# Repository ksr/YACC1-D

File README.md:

# YACC1-D — the definitive YACC1 tree

**Status (2026-09-28):** the single source of truth for YACC1, on GitHub at `github.com/ksr/YACC1-D`, migrated from
the old `YACCS/` folders on 2026-09-19/20. What is in the machine today: `docs/system/MACHINE.md`; which board
revisions exist and were made: `hardware/FABRICATED.md`; what is open: `BACKLOG.md`.

**Who made it:** YACC1 is my project: I designed and built the hardware and wrote the original microcode, monitor,
Tiny BASIC and emulator. Claude, Anthropic's AI, has been directly involved in the design, coding and documentation
since 2026; the header at the top of every source file says who wrote it. — Ken Rother

**Working on it:** `CLAUDE.md` (the working notes for Claude sessions) has the standing rules, the machine facts that
bite, where things are and how to build and test. On a new Mac: clone, `python3 tools/setup_check.py` (which tools are
missing, and the command for each), `make` (the C tools), then `make check`.

## What YACC1 is

YACC1 ("Yet Another Custom CPU") is a hand-built 8-bit TTL computer: an 8-bit accumulator and TMP register, eight
16-bit registers R0-R7, microcoded, on a 96-pin bus. The cards: backplane, a two-board sequencer (logic + microcode
memory), ALU, two index-register cards, memory (RAM, the 8K ROM, TMP registers), I/O (16550 UART console, switches,
LEDs, TIL311s), a 6845 video card (working since 2026-10-21; its VGA successor, V4, designed and not ordered), and
a bus tester for driving the bus by hand.

Around the hardware, all in this tree:

- **Firmware in the machine:** the microcode (a C generator that writes the sequencer's EEPROM image), the monitor
  ROM with its Intel-hex loader, BIOS vectors and video driver, and a Tiny BASIC.
- **Y1/OS:** a disk operating system on CompactFlash (P8XFS), with a shell, redirection and pipes, and some thirty-five
  `/bin` commands, most ported from P8X, among them `vi`, `sed`, `awk`, `pack` and `kermit`. It exists twice and is kept
  in step: `os/y1os.asm` (the real one) and `os/y1os.c` (its specification).
- **y1cc**, a C compiler for YACC1: a Python reference, a C twin, and nine passes that run under Y1/OS. Together with
  the on-target assembler `/bin/asm` they rebuild themselves byte for byte on the emulator (the self-host).
- **Host tools:** the RC/asm assembler, an instruction-level emulator, a microcode-level emulator that steps the real
  EEPROM image through models of the cards, loaders for the ROM monitor and the sequencer card, Kermit, the CF-card
  writer, and the KiCad board tooling.

Before this tree the work was spread over nine overlapping copies under `YACCS/` (Eagle variants, four git clones with
different histories, backups). YACC1-D keeps the *current* version of every board, program, tool, test and document in
one place, with everything superseded kept but frozen. `MIGRATION.md` and `migration/` record where every file came
from.

## The tree

```
YACC1-D/
├── README.md  CLAUDE.md  BACKLOG.md  MIGRATION.md
├── Makefile                  make (the C tools), make check (everything, ~11 min), os-test, cc-test, native-test, ...
├── docs/
│   ├── system/               MACHINE.md (what is built), architecture, memory map, microcode, OS plan
│   ├── isa/                  a timing diagram per instruction, the microcode review
│   ├── cards/                theory of operation, one per card
│   ├── programming/          assembler, monitor, OS, C compiler, emulators, memory map, I/O ports
│   ├── procedures/           bring-up, CF card, testing, Kermit
│   ├── bom/                  bills of material, one per card
│   ├── history/              dated design notes kept verbatim (2016-2021), presentations
│   ├── datasheets/           the list of third-party datasheets (the PDFs: ../private-resources/YACC1-D/)
│   └── references/           external papers and books
├── hardware/
│   ├── bus/                  backplane, bus template, bus jumpers, blank card
│   ├── cards/<card>/         one folder per card (below)
│   ├── libraries/            eagle/: the Eagle .lbr/.dru files the designs use
│   ├── mechanical/           card divider clips, switch template, spacers
│   ├── FABRICATED.md         every revision of every board: built, in the machine, or design only
│   ├── SCHEMATICS.md BOARDS.md   generated indexes of the schematic and board PDFs
│   ├── KICAD.md              the Eagle -> KiCad conversion and its netlist proof
│   └── reviews/              the indexes of the multi-card design reviews (2026-09-21: mechanical, datapath,
│                             control and I/O); the reviews themselves are in each board's own reviews/
├── firmware/                 code that runs INSIDE the machine
│   ├── microcode/            ucode-generator2 (C) -> test.hex, the sequencer EEPROM image
│   ├── monitor/  basic/      monitor.asm, basic.asm (+ candidates never burned)
│   ├── rom/                  shipped/ (the image to burn and what is burned), builds/, captured chips
│   └── abi/                  BIOS vectors, variable and port map (still to be written)
├── os/                       Y1/OS: y1os.asm + y1os.c, commands/ (C), commands-asm/ (asm.asm, basic.asm), lib_*.c,
│                             man/, docs/, Makefile -> os/disk.img
├── software/                 host-side toolchain (runs on the Mac)
│   ├── assembler/            RC/asm + yacc1.def
│   ├── emulator/             instruction-level emulator (the ISA reference)
│   ├── ucemu/                microcode-level emulator (test.hex through models of the cards, CF, video)
│   ├── y1dbg/                the debugger for ucemu (y1ucemu -D + a curses UI with the live video screen)
│   ├── gatemodel/            cards at gate level from their netlists (the video card for y1ucemu -G)
│   ├── compiler/             y1cc.py, c/ (y1cc.c and the passes cc1..cc9), lib/
│   ├── disassembler/         disasm2
│   └── ubasic-c/             the C uBASIC the assembly BASIC was ported from
├── embedded/                 Arduino sketches for the support cards, built against libraries/ only
│   ├── sequencer-card/       sequencer4 (the microcode loader in the machine), dumpram, deprecated/
│   ├── bus-tester/           bus-driver, bus-monitor, bus-test, led-switch-test
│   ├── clocker/              external single-step clock
│   ├── command-sender/       Processing host for bus-tester scripts (to be replaced by Python)
│   └── libraries/            vendored: YACC_Common_header.h (bus table), Adafruit_MCP23017 1.1.0
├── tools/                    host scripts: setup_check, verify_firmware/embedded, ucode_send, monload, cfcard,
│                             y1kermit, p8xfs, the KiCad/Eagle tooling, the tree audit
├── tests/                    os, compiler, native (self-host), asm, disasm, bench (the machine), monload, kermit,
│                             cfcard, video, sequencer, ucemu, y1dbg, memory, assembler, bus-tester-scripts
├── mk/                       shared make fragments
├── migration/                the 2026-09-19/20 migration's inventory, plan and logs
├── vm/                       manifests of VMs and legacy installers (the images live outside git)
├── media/                    photos of the boards
├── website/                  the project website: MkDocs over these docs (website/README.md), live at yacc1.cottageworker.com
└── archive/                  frozen, never edited: gen1-2015-2018 (the first YACC1), superseded-revisions,
                              eagle-projects, third-party, conflict-losers (older duplicates from the migration)
```

## Card folder layout (`hardware/cards/<card>/`)

```
<card>/
├── README.md        what the card is, current revision, what is built, open issues
├── kicad/<rev>/     KiCad 10 projects, GENERATED from the Eagle files by tools/eagle_to_kicad_all.py with a
│                    schematic-vs-board netlist proof (hardware/KICAD.md) - except where a MASTER marker says the
│                    KiCad project is hand-maintained and IS the design (memory v2.0, CF v1.0, video v1.1);
│                    those have a build.sh (route with Freerouting, DRC, gerbers, renders, BOM)
├── eagle/<rev>/     the Eagle originals, frozen; the active revision at the top, fab/ (what was sent to the board
│                    house), pdf/ (generated), bom/
│   └── deprecated/  every older revision, same shape
├── reviews/         the card's design reviews, one file per review (<rev>-<review>-<date>.md, or <rev>.md)
└── docs/            card-specific notes
```

| Card | In the machine | Designed, not built |
|---|---|---|
| backplane | V2.0 (8 slots) | |
| sequencer-logic | v2.1 | v2.2 "CPU off" switch (idea, BACKLOG) |
| sequencer-memory | V2.1 + EEPROM adaptor | |
| alu | V3.2 | |
| register (index registers) | 1.1, two cards (R0-R3, R4-R7) | |
| io | V1.1 | |
| memory | v1.3 | **v2.0**: v1.3 + the CompactFlash interface on P8/P9, finished for fabrication |
| video | V1.0, no 6845 fitted yet | **v1.1** (KiCad master), changes still to make before ordering |
| cf | | v1.0, a separate CF card, superseded by memory v2.0 |
| bus-tester | V1.1 (2016; a bench tool) | V3.1 (2020, never ordered) |
| mem-switch, mem-register | bring-up cards (switch ROM at $0000, 16-byte RAM at $0010), fitted when needed | |
| protocard, address-tmp | built (address-tmp retired) | |

Bus items live under `hardware/bus/`: backplane, bus-template V3.2, bus jumpers (built, obsolete, not fitted), blank
card V3.1 (built) and V3.2 (the template for new cards).

## Conventions

- One authoritative copy of anything. Duplicates were the whole problem.
- Lower-case, hyphenated directory names; no spaces (the Eagle tree's spaces broke scripts repeatedly).
- Binary images (ROM, microcode hex) are committed **with** their source and a script that rebuilds them and
  diffs against the committed file; `make check` does it for all of them.
- Every file is explained: `tools/audit_tree.py` must report 0 unexplained after every commit.
- Files that came from YACCS are edited only with a dated entry in `tools/patched_files.txt`.
- Third-party code and libraries are vendored under a folder that says so, with their licence.
- Anything under `archive/` or `deprecated/` is never edited.
- Every `.rtf` note has a generated Markdown twin beside it (`tools/rtf_to_md.py`).
- No git LFS. Very large binaries (the 142 MB presentation, installers, VM images) live outside git, listed in `vm/`.

## How the migration was settled

- Repo: `~/Developer/YACC1-D` on both Macs (out of iCloud Drive, which corrupts `.git`), on GitHub, no LFS.
- History: started fresh (the first commit is the migration); the old `ksr/YACC1-2020` repo is not grafted in.
- `archive/` is committed (about 186 MB), and so are the datasheets.
- Older board revisions that were built stay with their card under `eagle/deprecated/`;
  `archive/superseded-revisions/` holds designs never built and the old tree's snapshots.
- Monitor and BASIC: the 2026 builds in `firmware/rom/shipped` are current; the 2021 `8afde21` build (ON/OFF, break-in)
  is kept as a candidate, never burned.
- Build environment: every C tool has a plain Makefile (2026-09-20); the NetBeans `nbproject/` folders are kept but
  no longer needed.

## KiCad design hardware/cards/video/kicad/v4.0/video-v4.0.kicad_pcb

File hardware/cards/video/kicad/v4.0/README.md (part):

# Video card V4.0 (6845, VGA, 16 dots a count) - the circuit, the schematic, the routed board

The circuit as data, checked and simulated; its schematic; and the board, 250 mm long, every part placed and
**every connection routed** (2026-11-12; reviewed, changed and routed again 2026-11-13; routed once more
2026-11-14, its four clocks laid first). Not ordered, not built. The pre-order check (`pcb-check`, 2026-11-14)
finds no failure and leaves one warning: "The pre-order check", below. Changed on the routed board since, no track
moved: the oscillator's pin 1 tied to +5 V (2026-11-18); a place that takes the oscillator in a can of either
size, and the labels by the power LED set apart (2026-11-20). `v40_netlist.py` is the card's circuit (parts, nets, the pins left open), written from the design note
`docs/cards/video-v4.md` (section 5 the clock and the stage, 6 the text, 7 the graphics RAM's two modes, 8 the dot
path, 9 the ports).

`python3 v40_netlist.py` checks the wiring (in `make check`): every pin of every part on a net or listed as open, no
net with a single pin, no two outputs on one net, an output on every net of ICs, a capacitor for every IC, and the
text-only build.

`tests/video/v40_netsim.py` (in `make check`, about two minutes) runs the netlist as a circuit, gate for gate, with every
part's delays from its data sheet at both ends of their ranges: the proof that the wiring does what the note says,
and the timing check. The parts in the netlist are the ones it was run with: a 74HCT or 74LS part in place of a 74F
or 74ACT one is another circuit.

**134 parts, 46 ICs** (V2.0 has 40, the V3 design 47).

| Block | ICs | |
|---|---|---|
| Bus, ports, registers | IC1-IC9 | block select (74S85), port decode (74LS138), the strobes (2 x 74LS32), control 1 and control 2 (2 x 74HCT273), the status (74LS244), inverters and ANDs (74HCT04, 74HCT08) |
| The 6845 and the clock | IC10-IC13, OSC1, R20-R23 | the 6845, the 25.175 MHz oscillator, the dot counter (74F163A), the 6845's clock and DE's delay (74F74), inverters (74ACT04); 33 ohm in series with the dot clock (R20), D2 (R21), D3 (R22) and the stage's clock (R23) |
| Text | IC14-IC23 | the text RAM (IDT7134), the stage (2 x 74ACT574), the code register (74ACT574), the character generator (AT28C64B-15), the shifter (74F299), the cursor flag and the retimed dot (74F74), the load (74F21), 74ACT86, 74ACT08 |
| Graphics, left off in the text-only build | IC24-IC34, RN2 | the address multiplexers (4 x 74ACT157), the RAM (AS6C1008-55), the write buffer (74ACT244), the read latch (74ACT574), direct mode's read buffer (74HCT244), the byte latch (74ACT574), the shifter (74F299), WRQ and TXTONLY (74F74) |
| Slot logic, dots, syncs | IC35-IC40 | P56 and the read latch's clock (74F74), 74ACT32, 74ACT00, 74ACT11, the guns (74ACT02), the vertical sync's length (74HCT74) |
| PS/2 | IC41-IC46 | V2.0's section: ATmega328P, two latches, the status, the flags, the 7416 |

The references are new (this card keeps none of V1.3's or V2.0's numbers); the PS/2 section's nets are V2.0's.

## The simulation (2026-11-12; the hold margins and the counted addresses 2026-11-13)

The simulator and the models of the 74F and 74ACT parts and of the 128K RAM are `tests/video/netsim.py` (first
written for the V3 design's check); added are the 74ACT157, the 74ACT244 with its enable times, the text RAM's display
port, the character generator, a 6845 that steps a script of counts and checks the clock it is given, and the bus
as the microcode drives it, started at every phase of the dot counter. Eight corners: the 6845 slow or fast, the
parts all slow or all fast, and the two mixed corners that set rising outputs against falling ones. A clock's
series resistor (R20-R23) is a part with a delay of 0.3 to 2 ns: the resistor, its net's load and the wire, as one.

51 runs, none failing: the picture (every count's two characters and two bytes, the cursor's half, blanking, OR and
XOR, the pages, the colour bits), the window in slot mode at 3.5 MHz and in direct mode at 6 MHz (a write and two
reads at each of 32 phases of the count, the picture going on undisturbed; once more at 160 phases, 4 ns apart),
a read whose address was counted in the step before (a stack or a BRVR vector table in the window) at 2.8 MHz,
switching the mode at every phase with nothing written, the text-only build, the ports and the status, the syncs.

| Closest margins, all runs | To spare |
|---|---|
| Hold: the 6845's clock flip-flop takes the counter's D3 (IC12 pin 2) | 2.0 ns |
| Hold: the vertical sync's second flip-flop takes the first's output (IC40 pin 12) | 2.0 ns |
| Hold: the shifters' data, as the code register and the byte latch take the next byte | 2.5 ns |
| Hold: the shifters' load, as it ends | 3.7 ns |
| The retimed dot: a shifter's output through two gates to the flip-flop (set-up) | 5.6 ns |
| Hold: the 74ACT574s (the byte latch the closest) | 9.6 ns |
| Hold: the read latch | 10.7 ns |
| The shifters' load (the mode input's set-up) | 14.7 ns |
| The RAM's write pulse, 69.6 ns at its shortest | 24.6 ns over the 45 wanted |
| The RAM's data before the pulse ends | 34.6 ns |
| A byte read in slot mode at 3.5 MHz, on the bus before it is taken (160 phases) | 40 ns |
| The RAM to the read latch (set-up) | 52.1 ns |
| The text RAM (as the 70 ns grade) to the code register | 61.9 ns |
| A byte read in direct mode at 6 MHz, on the bus before it is taken | 88 ns |

The holds of 2 to 4 ns are all of one kind: a flip-flop takes what another, on the same clock edge, is changing.
They rest on the senders' least delays (2.7 ns for the 74F163A, 1.5 ns for a 74ACT574) and do not shrink with the
frequency; what they need is a clock that reaches the taker no later than the sender. The simulation prints the
least hold of each kind since the design review (its V4-5), which found that the first table here left them out.

`--limits`: the window works down to a microcode step of 531 ns in slot mode (a CPU clock of 3.76 MHz) and 248 ns in
direct mode (8.07 MHz), the parts slow, for an address that a register selected in the step puts on the bus. For an
address counted in the step before - a stack or a BRVR vector table in the window - slot mode works to 3.15 MHz
(the count within the window) and 2.97 MHz (into it), direct mode to 5.69 and 5.15 MHz: the note's rule 2.
`--faults`: 23 wiring faults put into the netlist in memory, one at a time (crossed bits, a missing gate input, the
wrong polarity): every one is reported by a run.

Not in it: the 6845's own minimum delays (its sheet gives none; 20 ns assumed, and the stage has 19 ns of hold from
a 6845 that answers in no time), Hitachi's 6845 (the figures are Motorola's sheet), a delay for each wire (the four
clock nets have one each, with their resistors; the others none), signal quality on the bus, and a bench.

## What the simulation changed in the netlist

- **A write pulse is always whole.** As first written, -WE in slot mode contained the CPU's strobe (V2.0's way), so
  a strobe that ended inside a pulse cut it short: a -WE of any width down to nothing, at a moment when the RAM's
  data lines still hold the display's byte. Now WRQ alone opens the pulse (WEP# = NAND(WRQ, P56)) and direct mode has
  a gate of its own (WED#); the microcode's step of hold after the strobe covers the rest of the slot. WRQ is held
  clear in direct mode (it was preset), so no pulse can come as slot mode begins.
- **The -WE pulse's flip-flop** has its D from the 74F21 and the read latch's clock flip-flop from the 74ACT11
  (they were the other way round): the first had 6 ns of set-up to spare behind the inverter, and has 11 now.

## What the netlist settles that the note left open

- **The read latch's clock** is a flip-flop's pulse in dots 8 and 0 (RDCK, IC35/B), so the latch takes the RAM's byte
  as a CPU slot ends with the whole slot for the access. The latch is a 74ACT574 for its 1 ns hold time.
- **The cursor flag** is taken with each code (IC20/A); only DE is delayed (SDE2, as dot 8 begins).
- **The status's VSYNC and DE** (IN PC bits 1 and 2) are the stage's, a count behind the 6845's pins.
- **The vertical sync** at the connector lasts from the staged VSYNC's rise to the second HSYNC after it: about 1.8
  lines, with either maker's 6845.
- **The text-only build** needs no resistor of its own: R8, R9 and R10 are fitted in both builds.
- **46 ICs**, where the note's estimate was 42 or 43: four 74F74 where it counted two, and an inverter and an AND
  package more.

## What the design review changed (2026-11-13)

`../../reviews/v4.0.md`: HIGH 0, MED 4, LOW 12, INFO 7. Nothing found says the card will not work; its status table
has what was done with each finding. In the circuit and on the board:

- **A 33 ohm resistor in series with each of the four clocks that cross the board**: R20 at the oscillator (the dot
  clock, seven 74F clock inputs), R21 and R22 at the counter's outputs (D2, D3), R23 at the inverter that makes the
  stage's clock. The nets between a source and its resistor are OSCO, QC, QD and STGO. A long track with several
  inputs along it and nothing at its end rings; the resistor damps it at the source.
- **The clock's column moved** two columns towards the bus connector, 30 mm: next to the multiplexers and the
  RAM's latches, and that much nearer the stage and the code register. It had been left behind when the columns
  were reordered for the first route.
- **The four clocks are laid before the rest of the board** (decided 2026-11-13, on the board since 2026-11-14):
  by `gen_v40.py clockroute`, as trees from their resistors, locked while Freerouting routes everything else. "The
  routing", below.
- **The VGA socket is a part**: Kycon K61X-E15S-NJ, whose drawing's hole pattern is KiCad's footprint within
  0.06 mm; its fifteen signal holes are drilled 1.1 mm, as the drawing asks (the footprint: 1.0).
- **On the silk**: a "1" at the oscillator's pin 1 (turned round, the can has VCC on its ground pin); the text-only
  legend names the capacitors too; labels 0.2 mm farther from the sockets' frames.
- **In the parts list**: an oscillator rated for the load, with a socket; two shunts; the jacks to be laid on their
  footprint before soldering.
- **In the simulation and the note**, no change to the board: the hold margins, the finer phases, the reads whose
  address is counted (a stack or a vector table in the window: rule 2 of the note's section 7).

Not changed: the shifters' load stays where it is (the review weighed moving it a dot earlier, for a hold that does
not rest on the parts' least delays: it would leave the load's set-up about 6 ns where it has 14.7).

## The schematic (2026-11-12)

`gen_v40.py` (made from the V3 and V2.0 designs' generators, in the git history; run it with KiCad's Python)
draws the schematic from the netlist: `video-v4.0.kicad_sch`, the root, and eight sheets. KiCad's own netlist of it
equals `v40_netlist.py` net for net (254 nets), and its electrical rules check finds nothing
(`reports/netlist.net`, `reports/erc.json`, `reports/video-v4.0-schematic.pdf`).

| Sheet | What is on it |
|---|---|
| 2 Bus and ports | the bus connector, the block select and its jumper, the port decode and strobes, the two control registers, the status |
| 3 CRTC and clock | the 6845, the oscillator, the dot counter, the 6845's clock, the stage registers, the clocks' series resistors |
| 4 Text | the text RAM, the code register, the character generator, the text shifter, the cursor flag |
| 5 Graphics RAM | the address multiplexers, the RAM, the write buffer, the two read paths, the byte latch, the shifter |
| 6 Slots | SELCPU, the write flip-flop, the -WE pulse, the RAM's -OE, the read latch's clock |
| 7 Dots and syncs | the two layers mixed, the retimed dot, the three guns, the syncs, the VGA socket |
| 8 PS2 | the ATmega328P, its latches, flags and status, the two jacks, the FTDI header |
| 9 Power | the power units, the decoupling capacitors, the LED |

| | |
|---|---|
| `gen_v40.py sch` | the local libraries and the schematic |
| `gen_v40.py project` | `video-v4.0.kicad_pro` and `.kicad_dru`: 0.25 mm tracks, 0.2 mm clearance, GND and VCC as planes |
| `gen_v40.py checknet reports/netlist.net` | KiCad's netlist of the schematic against `v40_netlist.py` |
| `gen_v40.py board reports/netlist.net <out.kicad_pcb>` | the unrouted board: every part placed, every pad on its net, the silkscreen placed |
| `gen_v40.py place <pcb>` | courtyards apart, everything inside the outline, the DIP sockets clear of each other and of the other parts |
| `gen_v40.py clockroute <unrouted.kicad_pcb> <out.kicad_pcb>` | the four clocks, and the stubs from their sources to the series resistors, laid as locked tracks and vias; nothing else touched |
| `gen_v40.py clocks <pcb> [report.txt]` | the clock nets as they are on a board: track, vias, the copper's length from each source to every input (`reports/clocks.txt`). Fails if an input is not reached or a clock's track is not locked |
| `gen_v40.py verify reports/netlist.net <pcb>` | 437 key connections pin by pin, in the schematic and on the board; the layers; the planes |
| `gen_v40.py drawing <pcb>` | `video-v4.0-placement.pdf` |
| `gen_v40.py bom` | `BOM.md` |
| `gen_v40.py fab <pcb>` | the order's files: `gerbers/` and `video-v4.0-gerbers.zip`. It orders nothing |
| `build.sh` | all of it, with the routing, the reports, the checks and, when they pass, the order's files |
| `SILK=1 build.sh` | the routed board kept: its silkscreen texts written and placed afresh, then the reports, the checks and the order's files |
| `gen_v40.py padnets reports/netlist.net <pcb>` | the routed board kept through a change of the netlist that needs no track: an open through-hole pad that the netlist now has on GND or VCC gets that net (the plane joins it when it is filled again). Any other difference between the board and the netlist is refused: it needs a route |
| `PADS=1 build.sh` | that change, whole: the schematic written anew and checked, `padnets`, the planes filled again, then the reports, the checks and the order's files. No part, track or via is touched (2026-11-18: the oscillator's pin 1) |
| `gen_v40.py refit reports/netlist.net <pcb> REF...` | the routed board kept through a part's new footprint or place: the named parts are taken off the board and put on again as the netlist and the placement have them today. A new pad where an old one stood, on the same net, keeps the copper routed to it. Refused if a track or via would be left without its pad, or if any pad then differs from the netlist: that needs a route |
| `gen_v40.py silk <pcb> [out] REF...` | the silkscreen for those parts alone: their labels and the legends that changed in `gen_v40.py`'s list are written and placed; every other text stays where it stands |
| `REFIT="OSC1" RELABEL="OSC1 JP1 J4" build.sh` | that change, whole: the schematic written anew and checked, `refit` for REFIT's parts, the labels of RELABEL's parts (REFIT's, if it is not given), the planes filled again, then the reports, the checks and the order's files. No other part, no track and no via is touched (2026-11-20: the oscillator's place, twice). `SILK=1 RELABEL="..." build.sh` does the labels alone |

## The board (2026-11-12): 250 mm, placed and routed

`build.sh` makes everything from `v40_netlist.py`: the schematic, the unrouted board, the clocks, the routing, the
reports and the checks. `video-v4.0.kicad_pcb` is the board: four layers (GND and VCC planes inside, the signals on the two
outer layers), the blank card's connector, 250.00 x 113.97 mm, 134 parts. `video-v4.0-placement.pdf` is its
placement drawing, on a landscape sheet as the board lies; `reports/video-v4.0-top.png` and `-bottom.png` show it
with the parts fitted.

**The length (decided 2026-11-12: 250 mm).** The 46 ICs stand in thirteen columns: eleven of 300-mil sockets and
two of 600-mil ones (the character generator over the text RAM, the graphics RAM over the 6845), a capacitor beside
every chip's VCC pin.

| | Card length |
|---|---|
| Every long card today, V2.0 with its 40 ICs among them | 218 mm |
| One column fewer, every column full to the last socket, at V2.0's spacing: no room left for the oscillator, the crystal, the jumpers or the resistors | 221 mm |
| This placement at V2.0's spacing (columns 14 mm apart) | 235 mm |
| This placement as it is: columns 15.24 mm apart | **250 mm** |

The card does not fit 218 mm. 235 mm is the shortest at V2.0's density, which routes on two signal layers only for
some component orders; the 15 mm from there to 250 are spent between the columns, as room to route.

**What stands where**, from the bus connector to the front edge: the port decode, the strobes and the block select,
with the block jumper SV1 at the bottom edge under it; the character generator over the text RAM (turned so that
its CPU port faces the bus and its display port the next column); the bus's inverters, the code register and the
stage, between the text RAM's display port and the 6845's MA pins; the graphics RAM over the 6845; the address
multiplexers, the oscillator under them; the clock, its counter at the bottom of the column beside the oscillator
(since the design review: it stood two columns farther on); the RAM's latches and buffers; the two shifters; the
slot logic; the dots' and syncs' gates; the control registers and the status; the PS/2 latches; the ATmega (turned
so that its crystal pins face the front).

**The layout rules** (2026-10-24 and after) are kept from the start. At the front edge, facing out: the VGA
socket, the two PS/2 jacks; beside them the INT jumper, the FTDI header and the power LED. The block jumper at the
bottom edge. Every reference with its type or value on the silk outside its part, placed by the generator clear of
every body and socket: none is under a part, none had to go into a legend. Each jumper position and the FTDI
header's pins labelled; `cottageworker.com` beside the card's name and revision. Bypass capacitors on 0.1-inch
leads.

**Every silk text reads with the card standing in the backplane, X1 down** (2026-11-18, the layout rules for every
board): KiCad's angle 270 for all of them (`gen_v40.py`'s `UP`), the card's name and `cottageworker.com` excepted,
which run up the side as drawn. Before, the texts read with the card lying flat, X1 at the left: 139 at 0, 146 at 90, 3 at 180 (X1's row letters), 3 at 270.
The texts turned to 270 are placed afresh, each IC's reference and type along the chip's long side, at its right as
drawn (above it, with the card standing), else at its left; KiCad's "keep upright" is off for the footprints' texts,
which would otherwise draw a 270 as a 90. With the card standing the FTDI header's and the block jumper's pins run
across it 2.54 mm apart: J4's pin names stand in two staggered lines under it, and SV1's rows carry the address
line's number (15, 14, 13, 12) under "A15-A12, ON=0". Done by `SILK=1 build.sh`: no part, track, via or plane moved;
of the gerbers only the front silkscreen differs.

**The two headers by the power LED (2026-11-20).** Their texts ran into one another: JP1's `INT-EN` into J4's first
pin name (`INT-EN GND`), `ON: PS/2 -INT` into the second (`-INTCTS`), and J4's note, one line of 25 mm, from under
JP1 to the power LED's resistor (`VCC NC R1`). Now each header has its own block under it, centred on it, the two
3 mm and more apart: under JP1 `JP1`, `INT-EN`, `ON: PS/2`, `-INT`; under J4 its pins' names in their two lines,
then `J4 FTDI`, `PIN 1 GND: BLACK` and `PIN 3 VCC: NC`. `LED1 PWR` and `R1 330` are where they were, and stand
alone. Silkscreen only: the two headers did not move.

**Labels given their place, and labels left alone (2026-11-20).** The placer keeps texts 0.15 mm apart and knows
nothing of what they say. `gen_v40.py`'s `LABEL_AT` gives a part's label its place (OSC1, JP1, J4), as on the I/O
card V1.2. And the silkscreen step can be told which parts' labels to write (`RELABEL`): run over the whole board
again, the placer moved the labels of parts nobody had touched - which of them find no room beside their part
decides the order of all the others - and beside the VGA socket's resistors it set R6's value next to R5's
reference. With `RELABEL` every other text stays where it stands: 145 of them on 2026-11-20.

**The routing.** The four clocks first, by the generator (below). Then Freerouting 1.9 for the other 492
connections, on the two outer layers, GND and VCC left to the planes: one run for each of four orders of the
components (`SEEDS`), at most 100 passes, then its optimiser (`MT=1`). Of the clean results - every connection
routed, no clearance or short of Freerouting's own making, the clocks as they were laid - the one with the fewest
vias is kept.

| | The board (2026-11-14, the clocks laid first) | The route of 2026-11-13 (`3d9a12f`: the review's changes, the clocks the router's own) | Before the review's changes (`feb171b`) | That one before optimising |
|---|---|---|---|---|
| Connections | 519 routed, 0 left | 519 routed, 0 left | 515 routed, 0 left | 515 routed, 0 left |
| Vias | 455, nine of them the clocks' | 377 | 350 | 469 |
| Track, all 0.25 mm | 27.6 m: 11.8 m on the front, 15.8 m on the back | 27.4 m: 11.3 m and 16.0 m | 26.2 m | 27.2 m |
| Planes | GND and VCC, one piece each | the same | the same | the same |

The four orders of the board's run: order 0 routed every connection, clean, 455 vias and 27.6 m after optimising
(kept); orders 1 and 3 stopped with two connections open and order 2 with one (orders 1 and 2 with shorts and
clearance errors of the router's making besides). 40 to 57 minutes of routing each, and 1 h 56 min of optimising
for the one that was complete: 2 h 40 min of running time in all. The run of 2026-11-13, with nothing fixed, had
three orders of four complete after about 40 minutes (order 0 kept; order 1 as good, 378 vias; order 3 left
IO-ADDR0 open at IC2 pin 1), and the board before the review's changes all four in 18 to 28 minutes. Fixed clocks
cost 78 vias and leave the router less room. (V2.0's board, 40 ICs on 218 mm, has 285 vias.) Freerouting does not
route the same file the same way twice: a repeat gives other figures of this size. The clocks are the same on
every build.

The connections were given as 499 here before. That is the most KiCad's rule check lists of one kind of error;
its connectivity count, which has no limit, says 515 for the first board and 519 for this one. Both boards have 0
open by that count too.

**The four clocks: laid first, and kept** (`gen_v40.py clockroute`; decided 2026-11-13). Freerouting does not
know a clock from any other net. On the route of 2026-11-13 the dot clock's farthest input was 188 mm from its
resistor and D2's 101; on another clean route of the same run, 137 and 228. Given the clocks alone on the empty
board it strings a net's inputs into one chain and leaves connections open. So the generator lays them: each net a
tree that grows from its series resistor one input at a time, the next input always the one that is cheapest to
reach, where the price is the new track plus `CK_ALPHA` (0.6) times the distance along the tree from the resistor
to the point where the branch leaves it (0 would give the least track, 1 every input its own shortest way). The
ways are found on a 0.25 mm grid over both outer layers, round every other net's pads at the board's clearance.
The tracks and vias are locked: KiCad's Specctra export hands them to Freerouting as fixed wiring, and its session
import leaves locked items alone. `build.sh` runs KiCad's rule check on the clocks alone before the routing and
`gen_v40.py clocks` on every result after it: an input that is not reached, or a clock track that is not locked,
fails the build.

Measured on the board (`reports/clocks.txt`: track, and the copper's length from the series resistor to each
input):

| Net | Track | Vias | From its resistor to each input |
|---|---|---|---|
| CK (R20; 10 mm from OSC1's output, pad 8, to R20) | 187 mm | 1 | IC11.2 16, IC12.3 35, IC19.12 46, IC20.11 54, IC33.12 77, IC35.3 125, IC35.11 134 mm |
| D2 (R21; 6 mm from IC11 pin 12 to R21) | 288 mm | 5 | IC34.3 18, IC20.3 34, IC38.11 45, IC32.11 64, IC13.3 81, IC21.9 84, IC36.1 86, IC17.11 91 mm |
| D3 (R22; 5 mm from IC11 pin 11 to R22) | 185 mm | 2 | IC12.11 41, IC12.2 50, IC14.6 73, IC13.1 75, IC24.2 108 mm |
| STG (R23; 8 mm from IC13 pin 2 to R23) | 172 mm | 1 | IC22.4 70, IC15.11 71, IC16.11 102 mm |

| The way to the farthest input | The board | The route of 2026-11-13 | Before the review's changes |
|---|---|---|---|
| CK | 134 mm | 188 mm | 166 mm |
| D2 | 91 mm | 101 mm | 197 mm |
| D3 | 108 mm | 117 mm | 128 mm |
| STG | 102 mm | 153 mm | 200 mm |

On the route of 2026-11-13 the clocks had 231, 246, 232 and 237 mm of track; before the review's changes 177,
267, 241 and 239.

**The clocks follow the layers' grain** (`CK_GRAIN`, `CK_VIA`). Freerouting lays this board's tracks across the
board on the top and up and down it on the bottom (on the route of 2026-11-13, 9.2 m of the top's 11.3 m ran
across and 8.9 m of the bottom's 16.0 m up and down), so that the layers can cross anywhere. A track the other way
is a wall on its layer: whatever crosses it needs two vias, or goes round. The first clock trees (2026-11-13) had
no vias and took the shortest way on either layer: 188 mm up and down on the top and 175 mm across on the bottom,
their farthest inputs at 131, 102, 98 and 90 mm. Round them the rest did not route: 5, 4, 7 and 12 connections
open in the four orders after all 100 passes (two hours), with 580 to 680 vias. So a step across a layer's grain
costs three times its length and a slanted one one and a half times, and a clock changes sides in a via (at the
price of 3 mm of track) as well as in its own pads. The trees now have 1 mm across the grain on each layer and
nine vias; CK's, D3's and STG's farthest inputs are 3 to 12 mm farther than the first trees', D2's 11 mm nearer.

**The checks, all passing** (`build.sh: ALL CHECKS PASS`): KiCad's netlist of the schematic equal to
`v40_netlist.py`; ERC nothing; DRC no unconnected item, no copper violation, schematic parity 0 (four warnings
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
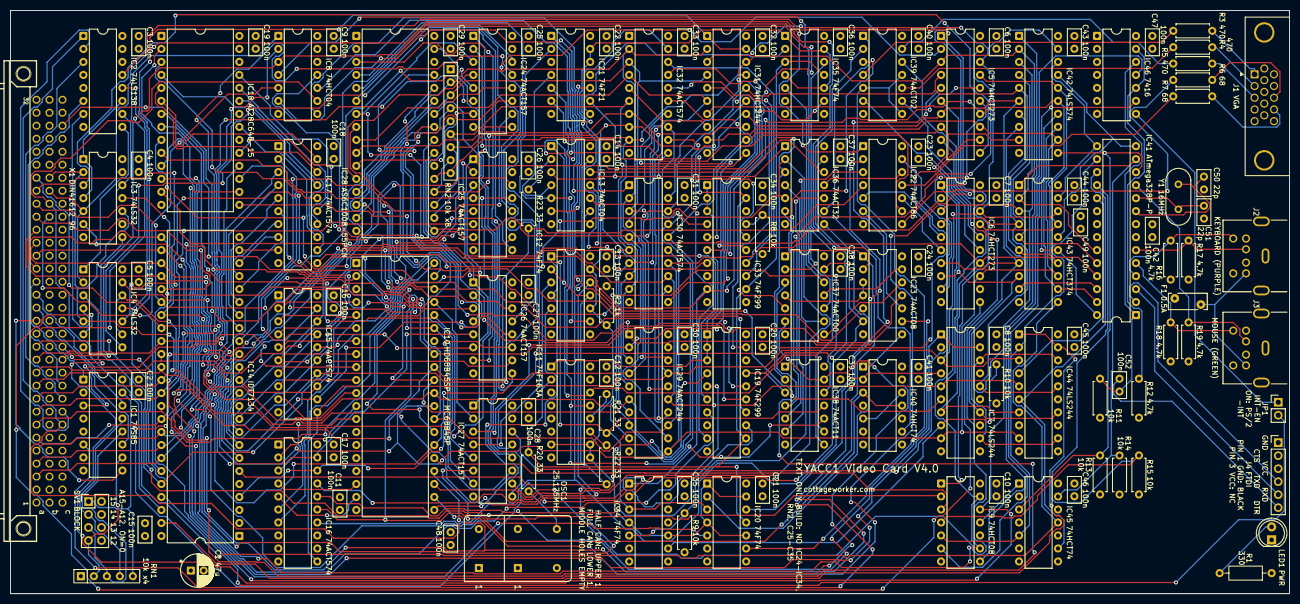
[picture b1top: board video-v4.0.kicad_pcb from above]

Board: 4 copper layers, 250.0 x 114.0 mm, 134 parts (0 on the bottom side), 254 nets.

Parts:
C1: 47u 16V; CP_Radial_D6.3mm_P2.50mm
C2, C3, C4, C5, C6, C7, C8, C9, C10, C11, C12, C13, C14, C15, C16, C17, C18, C19, C20, C21, C22, C23, C24, C25, C26, C27, C28, C29, C30, C31, C32, C33, C34, C35, C36, C37, C38, C39, C40, C41, C42, C43, C44, C45, C46, C47, C48, C49, C52: 100n; C_Disc_D5.0mm_W2.5mm_P2.50mm
C50, C51: 22p; C_Disc_D5.0mm_W2.5mm_P2.50mm
F1: 0.5A PTC; Fuse_Bourns_MF-RHT050
IC1: 74S85; DIP-16_W7.62mm
IC2: 74LS138; DIP-16_W7.62mm
IC3, IC4: 74LS32; DIP-14_W7.62mm
IC5, IC6: 74HCT273; DIP-20_W7.62mm
IC7, IC44: 74LS244; DIP-20_W7.62mm
IC8: 74HCT04; DIP-14_W7.62mm
IC9: 74HCT08; DIP-14_W7.62mm
IC10: HD68B45SP / MC68B45P; DIP-40_W15.24mm
IC11: 74F163A; DIP-16_W7.62mm
IC12, IC20, IC34, IC35: 74F74; DIP-14_W7.62mm
IC13: 74ACT04; DIP-14_W7.62mm
IC14: IDT7134; DIP-48_W15.24mm
IC15, IC16, IC17, IC30, IC32: 74ACT574; DIP-20_W7.62mm
IC18: AT28C64B-15; DIP-28_W15.24mm
IC19, IC33: 74F299; DIP-20_W7.62mm
IC21: 74F21; DIP-14_W7.62mm
IC22: 74ACT86; DIP-14_W7.62mm
IC23: 74ACT08; DIP-14_W7.62mm
IC24, IC25, IC26, IC27: 74ACT157; DIP-16_W7.62mm
IC28: AS6C1008-55PCN; DIP-32_W15.24mm
IC29: 74ACT244; DIP-20_W7.62mm
IC31: 74HCT244; DIP-20_W7.62mm
IC36: 74ACT32; DIP-14_W7.62mm
IC37: 74ACT00; DIP-14_W7.62mm
IC38: 74ACT11; DIP-14_W7.62mm
IC39: 74ACT02; DIP-14_W7.62mm
IC40, IC45: 74HCT74; DIP-14_W7.62mm
IC41: ATmega328P-P; DIP-28_W7.62mm
IC42: 74LS374; DIP-20_W7.62mm
IC43: 74HCT374; DIP-20_W7.62mm
IC46: 7416; DIP-14_W7.62mm
J1: VGA; DSUB-15-HD_Socket_Horizontal_P2.29x1.90mm_EdgePinOffset3.03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
J2: KEYBOARD; MiniDIN6_MD-60SM
J3: MOUSE; MiniDIN6_MD-60SM
J4: FTDI; PinHeader_1x06_P2.54mm_Vertical
JP1: INT-EN; PinHeader_1x02_P2.54mm_Vertical
LED1: PWR; LED_D5.0mm
OSC1: 25.175MHz; Oscillator_DIP-14_DIP-8
R1: 330; R_Axial_DIN0207_L6.3mm_D2.5mm_P10.16mm_Horizontal
R2: 1k; R_Axial_DIN0207_L6.3mm_D2.5mm_P7.62mm_Horizontal
R3, R4, R5: 470; R_Axial_DIN0207_L6.3mm_D2.5mm_P7.62mm_Horizontal
R6, R7: 68; R_Axial_DIN0207_L6.3mm_D2.5mm_P7.62mm_Horizontal
R8, R9, R10, R11, R13, R14, R15: 10k; R_Axial_DIN0207_L6.3mm_D2.5mm_P7.62mm_Horizontal
R12, R16, R17, R18, R19: 4.7k; R_Axial_DIN0207_L6.3mm_D2.5mm_P7.62mm_Horizontal
R20, R21, R22, R23: 33; R_Axial_DIN0207_L6.3mm_D2.5mm_P7.62mm_Horizontal
RN1: 10k x4; R_Array_SIP5
RN2: 10k x8; R_Array_SIP9
SV1: BLOCK; PinHeader_2x04_P2.54mm_Vertical
X1: DIN41612 96; FABC96R
Y1: 16MHz; Crystal_HC49-U_Vertical

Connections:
/-INT: JP1.2, X1.C13
/-IO-RD: IC3.5, IC3.13, IC4.2, IC22.1, X1.B25
/-IO-WR: IC3.2, IC3.10, IC4.5, IC10.22, IC22.2, X1.B26
/-MEM-RD: IC8.5, IC14.43, X1.B23
/-MEM-WR: IC8.9, IC14.46, X1.B24
/-RESET: IC5.1, IC6.1, IC9.9, IC9.13, IC10.2, X1.C30
/-VMA: IC8.1, X1.C12
/ADDR0: IC14.42, IC24.3, X1.A3
/ADDR1: IC14.41, IC24.6, X1.A4
/ADDR2: IC14.40, IC24.10, X1.A5
/ADDR3: IC14.39, IC24.13, X1.A6
/ADDR4: IC14.38, IC25.3, X1.A7
/ADDR5: IC14.37, IC25.6, X1.A8
/ADDR6: IC14.36, IC25.10, X1.A9
/ADDR7: IC14.35, IC25.13, X1.A10
/ADDR8: IC14.34, IC26.3, X1.A11
/ADDR9: IC14.33, IC26.6, X1.A12
/ADDR10: IC14.44, IC26.10, X1.A13
/ADDR11: IC8.3, IC23.2, X1.A14
/ADDR12: IC1.9, X1.A15
/ADDR13: IC1.11, X1.A16
/ADDR14: IC1.14, X1.A17
/ADDR15: IC1.1, X1.A18
/BLUE: J1.3, R5.2
/BOARDSEL: IC1.6, IC23.1, IC37.1
/BUSY: IC41.17, IC44.6, IC45.9
/BX: IC36.10, IC38.6
/CA0: IC17.19, IC18.6
/CA1: IC17.18, IC18.5
/CA2: IC17.17, IC18.4
/CA3: IC17.16, IC18.3
/CA4: IC17.15, IC18.25
/CA5: IC17.14, IC18.24
/CA6: IC17.13, IC18.21
/CA7: IC17.12, IC18.23
/CG0: IC18.11, IC19.7
/CG1: IC18.12, IC19.13
/CG2: IC18.13, IC19.6
/CG3: IC18.15, IC19.14
/CG4: IC18.16, IC19.5
/CG5: IC18.17, IC19.15
/CG6: IC18.18, IC19.4
/CG7: IC18.19, IC19.16
/CK: IC11.2, IC12.3, IC19.12, IC20.11, IC33.12, IC35.3, IC35.11, R20.2
/CMDCK: IC3.8, IC43.11, IC45.11
/CPAGE: IC5.12, IC27.13
/CRTCCK: IC10.21, IC12.5
/CRTCCS#: IC9.3, IC10.25
/CRTCE: IC10.23, IC22.3
/CTL1CK: IC3.3, IC5.11
/CTL2CK: IC4.6, IC6.11
/CURF: IC18.2, IC20.5
/CURFD: IC20.2, IC23.8
/CURH: IC6.5, IC22.5
/CURSOR: IC10.19, IC16.5
/CURX: IC22.6, IC23.10
/D0: IC11.14, IC21.1, IC38.9
/D1: IC11.13, IC13.5, IC21.2, IC38.10
/D1N: IC13.6, IC21.10
/D2: IC13.3, IC17.11, IC20.3, IC21.9, IC32.11, IC34.3, IC36.1, IC38.11, R21.2
/D2N: IC13.4, IC21.4
/D3: IC12.2, IC12.11, IC13.1, IC14.6, IC24.2, R22.2
/DATA0: IC5.3, IC6.3, IC7.18, IC10.33, IC14.25, IC29.2, IC30.19, IC31.18, IC42.2, IC43.3, IC44.18, X1.A19
/DATA1: IC5.4, IC6.4, IC7.16, IC10.32, IC14.26, IC29.4, IC30.18, IC31.16, IC42.5, IC43.4, IC44.16, X1.A20
/DATA2: IC5.7, IC6.7, IC7.14, IC10.31, IC14.27, IC29.6, IC30.17, IC31.14, IC42.6, IC43.7, IC44.14, X1.A21
/DATA3: IC5.8, IC6.8, IC7.12, IC10.30, IC14.28, IC29.8, IC30.16, IC31.12, IC42.9, IC43.8, IC44.12, X1.A22
/DATA4: IC5.13, IC6.13, IC7.9, IC10.29, IC14.29, IC29.11, IC30.15, IC31.9, IC42.12, IC43.13, IC44.9, X1.A23
/DATA5: IC5.14, IC6.14, IC7.7, IC10.28, IC14.30, IC29.13, IC30.14, IC31.7, IC42.15, IC43.14, IC44.7, X1.A24
/DATA6: IC5.17, IC6.17, IC7.5, IC10.27, IC14.31, IC29.15, IC30.13, IC31.5, IC42.16, IC43.17, IC44.5, X1.A25
/DATA7: IC5.18, IC6.18, IC7.3, IC10.26, IC14.32, IC29.17, IC30.12, IC31.3, IC42.19, IC43.18, IC44.3, X1.A26
/DE: IC10.18, IC16.4
/DPAGE: IC5.15, IC27.14
/DRDOE#: IC4.11, IC31.1, IC31.19
/FDTR: C52.1, J4.6
/FRX: IC41.3, J4.5
/FTX: IC41.2, J4.4
/FULL: IC9.5, IC41.16, IC44.2, IC45.5
/FULLCLR#: IC9.11, IC45.1
/GA0: IC24.4, IC28.12
/GA1: IC24.7, IC28.11
/GA2: IC24.9, IC28.10
/GA3: IC24.12, IC28.9
/GA4: IC25.4, IC28.8
/GA5: IC25.7, IC28.7
/GA6: IC25.9, IC28.6
/GA7: IC25.12, IC28.5
/GA8: IC26.4, IC28.27
/GA9: IC26.7, IC28.26
/GA10: IC26.9, IC28.23
/GA11: IC26.12, IC28.25
/GA12: IC27.4, IC28.4
/GA13: IC27.7, IC28.28
/GA14: IC27.9, IC28.3
/GA15: IC27.12, IC28.31
/GD0: IC28.13, IC29.18, IC30.2, IC31.2, IC32.2, RN2.2
/GD1: IC28.14, IC29.16, IC30.3, IC31.4, IC32.3, RN2.3
/GD2: IC28.15, IC29.14, IC30.4, IC31.6, IC32.4, RN2.4
/GD3: IC28.17, IC29.12, IC30.5, IC31.8, IC32.5, RN2.5
/GD4: IC28.18, IC29.9, IC30.6, IC31.11, IC32.6, RN2.6
/GD5: IC28.19, IC29.7, IC30.7, IC31.13, IC32.7, RN2.7
/GD6: IC28.20, IC29.5, IC30.8, IC31.15, IC32.8, RN2.8
/GD7: IC28.21, IC29.3, IC30.9, IC31.17, IC32.9, RN2.9
/GDOT: IC33.17, IC38.4, IC39.3, R8.1
/GFXON: IC4.13, IC5.16, IC13.9, IC33.9, IC34.1
/GL0: IC32.19, IC33.7
/GL1: IC32.18, IC33.13
/GL2: IC32.17, IC33.6
/GL3: IC32.16, IC33.14
/GL4: IC32.15, IC33.5
/GL5: IC32.14, IC33.15
/GL6: IC32.13, IC33.4
/GL7: IC32.12, IC33.16
/GOE#: IC28.24, IC38.12
/GRDOE#: IC4.9, IC4.12, IC37.6, IC38.13
/GREEN: J1.2, R4.2
/GSEL: IC23.3, IC23.4, IC37.4
/GWE#: IC23.11, IC28.29, IC29.1, IC29.19
/GWR: IC23.6, IC34.2, IC37.13
/HSB: IC22.8, R6.1
/HSOUT: J1.13, R6.2
/HSYNC: IC10.39, IC16.6
/INTG: IC9.6, IC46.9
/INTOC: IC46.8, JP1.1
/INTREQ: IC9.4, IC41.18, R15.1
/IO-ADDR0: IC2.1, IC10.24, X1.C7
/IO-ADDR1: IC2.2, X1.C8
/IO-ADDR2: IC2.3, X1.C9
/IO-ADDR3: IC2.6, X1.C10
/KCLK: IC41.4, J2.5, R16.1
/KDAT: IC41.6, J2.1, R17.1
/LDDATA: IC41.12, IC42.11, IC45.3, R13.1
/LEDA: LED1.2, R1.2
/MA0: IC10.4, IC15.2
/MA1: IC10.5, IC15.3
/MA2: IC10.6, IC15.4
/MA3: IC10.7, IC15.5
/MA4: IC10.8, IC15.6
/MA5: IC10.9, IC15.7
/MA6: IC10.10, IC15.8
/MA7: IC10.11, IC15.9
/MA8: IC10.12, IC16.2
/MA9: IC10.13, IC16.3
/MCLK: IC41.5, J3.5, R18.1
/MD0: IC41.23, IC42.3, IC43.2
/MD1: IC41.24, IC42.4, IC43.5
/MD2: IC41.25, IC42.7, IC43.6
/MD3: IC41.26, IC42.8, IC43.9
/MD4: IC41.27, IC42.13, IC43.12
/MD5: IC41.28, IC42.14, IC43.15
/MD6: IC41.14, IC42.17, IC43.16
/MD7: IC41.15, IC42.18, IC43.19
/MDAT: IC41.11, J3.1, R19.1
/MEMRD: IC8.6, IC37.5
/MEMWR: IC8.8, IC23.5
/MRST: C52.2, IC41.1, IC46.12, R11.1
/NADDR11: IC8.4, IC37.2
/NGFX: IC4.10, IC13.8, IC36.2, IC36.5, IC37.12
/NGOT: IC36.9, IC39.1
/NSHS: IC8.10, IC22.9
/NSVS: IC13.12, IC36.12
/OFFB: IC6.19, IC39.12
/OFFG: IC6.16, IC39.9
/OFFR: IC6.15, IC39.6
/OSCO: OSC1.8, R20.1
/P56: IC35.5, IC37.10
/P56D: IC21.8, IC35.2
/PDOE#: IC4.3, IC9.12, IC42.1
/PLANE0: IC5.2, IC26.13
/PLANE1: IC5.5, IC27.3
/PLANE2: IC5.6, IC27.6
/PLANE3: IC5.9, IC27.10
/POLH: IC6.6, IC22.10
/POLV: IC6.9, IC22.13
/PS2VCC: F1.2, J2.4, J3.4
/PSEL_A#: IC2.13, IC9.1
/PSEL_B#: IC2.12, IC9.2
/PSEL_C#: IC2.11, IC3.1, IC3.4
/PSEL_D#: IC2.10, IC3.9, IC3.12
/PSEL_E#: IC2.9, IC4.1
/PSEL_F#: IC2.7, IC4.4
/PSTOE#: IC3.11, IC44.1, IC44.19
/PU: IC11.1, IC11.7, IC11.9, IC11.10, IC12.1, IC12.4, IC12.10, IC12.13, IC19.1, IC19.2, IC19.3, IC20.1, IC20.4, IC20.10, IC20.13, IC21.12, IC21.13, IC33.1, IC33.2, IC33.3, IC34.4, IC34.10, IC35.1, IC35.4, IC35.10, IC35.13, R2.2
/QC: IC11.12, R21.1
/QD: IC11.11, R22.1
/RA0: IC10.38, IC18.10, IC26.14
/RA1: IC10.37, IC18.9, IC27.2
/RA2: IC10.36, IC18.8, IC27.5
/RA3: IC10.35, IC18.7, IC27.11
/RDCK: IC30.11, IC35.9
/RDCKD: IC35.12, IC38.8
/RDCMD: IC41.13, IC43.1, IC45.13, R14.1
/RED: J1.1, R3.2
/RESETB: IC9.8, IC46.11
/RESETH: IC46.10, IC46.13, R12.1
/SA0: IC14.7, IC15.19, IC24.5
/SA1: IC14.8, IC15.18, IC24.11
/SA2: IC14.9, IC15.17, IC24.14
/SA3: IC14.10, IC15.16, IC25.2
/SA4: IC14.11, IC15.15, IC25.5
/SA5: IC14.12, IC15.14, IC25.11
/SA6: IC14.13, IC15.13, IC25.14
/SA7: IC14.14, IC15.12, IC26.2
/SA8: IC14.15, IC16.19, IC26.5
/SA9: IC14.4, IC16.18, IC26.11
/SCUR: IC16.16, IC23.9
/SDE: IC7.6, IC12.12, IC16.17
/SDE2: IC12.9, IC21.5
/SEL0: IC1.10, RN1.2, SV1.7
/SEL1: IC1.12, RN1.3, SV1.5
/SEL2: IC1.13, RN1.4, SV1.3
/SEL3: IC1.15, RN1.5, SV1.1
/SELCPU: IC24.1, IC25.1, IC26.1, IC27.1, IC36.3, IC38.2
/SHS: IC8.11, IC16.15, IC40.3, IC40.11
/SRC: IC41.19, IC44.4
/SRDOE#: IC4.8, IC30.1
/STATOE#: IC3.6, IC7.1, IC7.19
/STG: IC15.11, IC16.11, IC22.4, R23.2
/STGO: IC13.2, R23.1
/SVS: IC7.4, IC13.13, IC16.14, IC40.2
/TDOT: IC19.17, IC38.3, IC39.2
/TEXTOFF: IC6.2, IC13.11
/TEXTON: IC13.10, IC19.9
/TLOAD: IC19.19, IC21.6, IC33.19
/TXTCE#: IC14.47, IC37.3
/TXTONLY: IC7.8, IC34.9, R10.1
/VB: IC39.13, R5.1
/VD0: IC14.16, IC17.2
/VD1: IC14.17, IC17.3
/VD2: IC14.18, IC17.4
/VD3: IC14.19, IC17.5
/VD4: IC14.20, IC17.6
/VD5: IC14.21, IC17.7
/VD6: IC14.22, IC17.8
/VD7: IC14.23, IC17.9
/VG: IC39.10, R4.1
/VIDN: IC20.12, IC36.8
/VIDNQ: IC20.9, IC39.5, IC39.8, IC39.11
/VMA: IC1.3, IC8.2
/VQ1: IC40.5, IC40.12
/VQ2: IC36.13, IC40.9
/VR: IC39.4, R3.1
/VS2#: IC22.12, IC36.11
/VSB: IC22.11, R7.1
/VSOUT: J1.14, R7.2
/VSYNC: IC10.40, IC16.7
/WED#: IC23.13, IC37.11
/WEP#: IC23.12, IC37.8
/WOE: IC36.6, IC38.1
/WRQ: IC34.5, IC36.4, IC37.9, R9.1
/XORM: IC5.19, IC38.5
/XT1: C50.1, IC41.9, Y1.1
/XT2: C51.1, IC41.10, Y1.2
GND: C1.2, C2.2, C3.2, C4.2, C5.2, C6.2, C7.2, C8.2, C9.2, C10.2, C11.2, C12.2, C13.2, C14.2, C15.2, C16.2, C17.2, C18.2, C19.2, C20.2, C21.2, C22.2, C23.2, C24.2, C25.2, C26.2, C27.2, C28.2, C29.2, C30.2, C31.2, C32.2, C33.2, C34.2, C35.2, C36.2, C37.2, C38.2, C39.2, C40.2, C41.2, C42.2, C43.2, C44.2, C45.2, C46.2, C47.2, C48.2, C49.2, C50.2, C51.2, IC1.2, IC1.4, IC1.8, IC2.4, IC2.5, IC2.8, IC3.7, IC4.7, IC5.10, IC6.10, IC7.2, IC7.10, IC7.17, IC8.7, IC8.13, IC9.7, IC10.1, IC10.3, IC11.3, IC11.4, IC11.5, IC11.6, IC11.8, IC12.7, IC13.7, IC14.1, IC14.3, IC14.5, IC14.24, IC14.45, IC15.1, IC15.10, IC16.1, IC16.8, IC16.9, IC16.10, IC17.1, IC17.10, IC18.14, IC18.20, IC18.22, IC19.10, IC19.11, IC19.18, IC20.7, IC21.7, IC22.7, IC23.7, IC24.8, IC24.15, IC25.8, IC25.15, IC26.8, IC26.15, IC27.8, IC27.15, IC28.2, IC28.16, IC28.22, IC29.10, IC30.10, IC31.10, IC32.1, IC32.10, IC33.10, IC33.11, IC33.18, IC34.7, IC34.11, IC34.12, IC34.13, IC35.7, IC36.7, IC37.7, IC38.7, IC39.7, IC40.7, IC41.8, IC41.22, IC42.10, IC43.10, IC44.8, IC44.10, IC44.11, IC44.13, IC44.15, IC44.17, IC45.7, IC46.1, IC46.3, IC46.5, IC46.7, J1.5, J1.6, J1.7, J1.8, J1.10, J1.SH, J2.3, J2.S, J3.3, J3.S, J4.1, J4.2, LED1.1, OSC1.7, R8.2, R9.2, R15.2, SV1.2, SV1.4, SV1.6, SV1.8, X1.A1, X1.A32, X1.B1, X1.B32, X1.C1, X1.C32
VCC: C1.1, C2.1, C3.1, C4.1, C5.1, C6.1, C7.1, C8.1, C9.1, C10.1, C11.1, C12.1, C13.1, C14.1, C15.1, C16.1, C17.1, C18.1, C19.1, C20.1, C21.1, C22.1, C23.1, C24.1, C25.1, C26.1, C27.1, C28.1, C29.1, C30.1, C31.1, C32.1, C33.1, C34.1, C35.1, C36.1, C37.1, C38.1, C39.1, C40.1, C41.1, C42.1, C43.1, C44.1, C45.1, C46.1, C47.1, C48.1, C49.1, F1.1, IC1.16, IC2.16, IC3.14, IC4.14, IC5.20, IC6.20, IC7.11, IC7.13, IC7.15, IC7.20, IC8.14, IC9.10, IC9.14, IC10.20, IC11.16, IC12.14, IC13.14, IC14.2, IC14.48, IC15.20, IC16.20, IC17.20, IC18.27, IC18.28, IC19.20, IC20.14, IC21.14, IC22.14, IC23.14, IC24.16, IC25.16, IC26.16, IC27.16, IC28.30, IC28.32, IC29.20, IC30.20, IC31.20, IC32.20, IC33.20, IC34.14, IC35.14, IC36.14, IC37.14, IC38.14, IC39.14, IC40.1, IC40.4, IC40.10, IC40.13, IC40.14, IC41.7, IC41.20, IC42.20, IC43.20, IC44.20, IC45.2, IC45.4, IC45.10, IC45.12, IC45.14, IC46.14, OSC1.1, OSC1.4, OSC1.11, OSC1.14, R1.1, R2.1, R10.2, R11.2, R12.2, R13.2, R14.2, R16.2, R17.2, R18.2, R19.2, RN1.1, RN2.1, X1.A2, X1.A31, X1.B2, X1.B31, X1.C2, X1.C31

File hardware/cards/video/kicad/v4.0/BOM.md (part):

# Video card V4.0 - bill of materials

GENERATED by `gen_v40.py bom` from `v40_netlist.py` (2026-11-20) - do not edit. 134 parts. Buy every IC in a socket (the 6845, the IDT7134, the 28C64, the RAM, the oscillator and the ATmega at least): 19 x 14-pin 7.62 mm, 7 x 16-pin 7.62 mm, 15 x 20-pin 7.62 mm, 1 x 28-pin 7.62 mm, 1 x 28-pin 15.24 mm, 1 x 32-pin 15.24 mm, 1 x 40-pin 15.24 mm, 1 x 48-pin 15.24 mm, and for the oscillator the socket of its can's size, or four single socket pins in the holes of the can that is used and none in the other two. **Text-only build**: leave off the parts marked *off*; nothing is fitted for that build only.

| Qty | Value | Footprint | References | Text-only | Buy / note |
|---|---|---|---|---|---|
| 1 | 47u 16V | CP_Radial_D6.3mm_P2.50mm | C1 |  | 47 uF electrolytic, 16 V or more, radial 6.3 mm, 2.5 mm pitch |
| 38 | 100n | C_Disc_D5.0mm_W2.5mm_P2.50mm | C2, C3, C4, C5, C6, C7, C8, C9, C10, C11, C12, C13, C14, C15, C16, C17, C18, C19, C20, C21, C22, C23, C24, C36, C37, C38, C39, C40, C41, C42, C43, C44, C45, C46, C47, C48, C49, C52 |  | ceramic X7R, 50 V, 2.5 mm lead spacing |
| 11 | 100n | C_Disc_D5.0mm_W2.5mm_P2.50mm | C25, C26, C27, C28, C29, C30, C31, C32, C33, C34, C35 | off | ceramic X7R, 50 V, 2.5 mm lead spacing |
| 2 | 22p | C_Disc_D5.0mm_W2.5mm_P2.50mm | C50, C51 |  | ceramic C0G (NP0), 50 V, 2.5 mm lead spacing |
| 1 | 0.5A PTC | Fuse_Bourns_MF-RHT050 | F1 |  | Bourns MF-RHT050 (0.5 A hold, radial) |
| 1 | 74S85 | DIP-16_W7.62mm | IC1 |  | 74S85 (the V1.x card's; a 74LS85 also works) |
| 1 | 74LS138 | DIP-16_W7.62mm | IC2 |  | port decode: Y2..Y7 = PA..PF (IO-ADDR3 = 1) |
| 2 | 74LS32 | DIP-14_W7.62mm | IC3, IC4 |  |  |
| 2 | 74HCT273 | DIP-20_W7.62mm | IC5, IC6 |  |  |
| 2 | 74LS244 | DIP-20_W7.62mm | IC7, IC44 |  |  |
| 1 | 74HCT04 | DIP-14_W7.62mm | IC8 |  | VMA, NOT ADDR11, MEMRD, MEMWR, NOT HSYNC; one spare |
| 1 | 74HCT08 | DIP-14_W7.62mm | IC9 |  | the 6845's -CS; INTREQ AND FULL; the -RESET buffer for IC46; FULL's clear |
| 1 | HD68B45SP / MC68B45P | DIP-40_W15.24mm | IC10 |  | HD68B45SP (Hitachi) or MC68B45P (Motorola), the 2 MHz (B) bus grade for a CPU clock above 1 MHz (a 6 MHz CPU's OUT gives E 333 ns high); the card's 1.573 MHz character clock is inside every grade. At the machine's 1 MHz the V1.0 card's 6845 fits |
| 1 | 74F163A | DIP-16_W7.62mm | IC11 |  | 74F163A: the type the timing is worked out with (not LS or HCT) |
| 3 | 74F74 | DIP-14_W7.62mm | IC12, IC20, IC35 |  | 74F74 |
| 1 | 74ACT04 | DIP-14_W7.62mm | IC13 |  | STG (NOT D3), NOT D2, NOT D1, NOT GFX-ON, TEXT-ON, NOT VSYNC |
| 1 | IDT7134 | DIP-48_W15.24mm | IC14 |  | IDT7134 SA or LA, 55 ns (the commercial grade; the sheet's slowest is 70 ns, there is no 90), DIP-48; or the V1.0 card's chip |
| 3 | 74ACT574 | DIP-20_W7.62mm | IC15, IC16, IC17 |  |  |
| 1 | AT28C64B-15 | DIP-28_W15.24mm | IC18 |  | AT28C64B-15PU (Microchip), 150 ns, burned with the card's character generator image (256 glyphs of 8 x 16 and their cursor forms: to be made) |
| 1 | 74F299 | DIP-20_W7.62mm | IC19 |  | 74F299 |
| 1 | 74F21 | DIP-14_W7.62mm | IC21 |  | 74F21 |
| 1 | 74ACT86 | DIP-14_W7.62mm | IC22 |  | the 6845's E; the cursor's half; the two syncs' polarity |
| 1 | 74ACT08 | DIP-14_W7.62mm | IC23 |  | the window's select and write strobe; the cursor flag's D; the RAM's -WE |
| 4 | 74ACT157 | DIP-16_W7.62mm | IC24, IC25, IC26, IC27 | off |  |
| 1 | AS6C1008-55PCN | DIP-32_W15.24mm | IC28 | off | AS6C1008-55PCN (Alliance, 128K x 8, 55 ns, 600-mil DIP-32) |
| 1 | 74ACT244 | DIP-20_W7.62mm | IC29 | off | SN74ACT244N: the type the timing check was run with; TI's package list marked the DIP 'last time buy' in 2026-11 |
| 1 | 74ACT574 | DIP-20_W7.62mm | IC30 | off | 74ACT574: its hold time (1 ns) is what the read latch's clock is worked out with; it drives the bus |
| 1 | 74HCT244 | DIP-20_W7.62mm | IC31 | off | 74HCT244; a 74ACT244 (24 mA) if DATA0's low level during a window read is above 0.5 V (V2.0's R2-6) |
| 1 | 74ACT574 | DIP-20_W7.62mm | IC32 | off | graphics display byte latch (dots 4 and 12) |
| 1 | 74F299 | DIP-20_W7.62mm | IC33 | off | 74F299 |
| 1 | 74F74 | DIP-14_W7.62mm | IC34 | off | 74F74 |
| 1 | 74ACT32 | DIP-14_W7.62mm | IC36 |  | SELCPU; a write waiting or direct mode (for the RAM's -OE); the mixed dot; VSYNC cut to two lines |
| 1 | 74ACT00 | DIP-14_W7.62mm | IC37 |  | the text RAM's -CE; a window read; slot mode's write pulse; direct mode's write strobe |
| 1 | 74ACT11 | DIP-14_W7.62mm | IC38 |  | the RAM's -OE; text AND graphics AND XOR; the read latch's clock flip-flop's D (dots 7 and 15) |
| 1 | 74ACT02 | DIP-14_W7.62mm | IC39 |  | NOR(text, graphics); the three guns' gates |
| 2 | 74HCT74 | DIP-14_W7.62mm | IC40, IC45 |  |  |
| 1 | ATmega328P-P | DIP-28_W7.62mm | IC41 |  | ATmega328P-PU with the Arduino Uno bootloader burned (ISP) before fitting |
| 1 | 74LS374 | DIP-20_W7.62mm | IC42 |  | PS/2 data latch (IN PE) |
| 1 | 74HCT374 | DIP-20_W7.62mm | IC43 |  | PS/2 command latch (OUT PD) |
| 1 | 7416 | DIP-14_W7.62mm | IC46 |  | open collector: the ATmega's reset, -INT |
| 1 | VGA | DSUB-15-HD_Socket_Horizontal_P2.29x1.90mm_EdgePinOffset3.03mm_Housed_MountingHolesOffset4.94mm | J1 |  | Kycon K61X-E15S-NJ (its drawing rev A5, 2017-12-31): right-angle HD-15 socket, 4-40 jackscrews fitted, board locks. Its hole pattern is the footprint's within 0.06 mm (rows 1.95 mm apart for the footprint's 1.90, the front row 3.05 mm from the board's edge for 3.03, the locks 5.00 mm from it for 4.94, 24.99 mm apart for 25.0); the signal holes are drilled 1.1 mm for it. NOT a part with rows 2.54 mm apart (Amphenol ICD15S13E..., NorComp 181-015-...): another pattern, 8.89 mm from the edge. Lay the part on a 1:1 print of the board before ordering |
| 1 | KEYBOARD | MiniDIN6_MD-60SM | J2 |  | Same Sky (CUI Devices) MD-60SM, date code after 2022-03-03 (the footprint follows that layout): lay the part on the footprint before soldering, a buyer cannot choose the date code |
| 1 | MOUSE | MiniDIN6_MD-60SM | J3 |  | Same Sky (CUI Devices) MD-60SM, as J2 |
| 1 | FTDI | PinHeader_1x06_P2.54mm_Vertical | J4 |  | 1x6 pin header; a 5 V FTDI cable (TTL-232R-5V) or a 5 V FTDI Basic |
| 1 | INT-EN | PinHeader_1x02_P2.54mm_Vertical | JP1 |  | 1x2 pin header and one 2.54 mm shunt (fitted: the card may drive -INT) |
| 1 | PWR | LED_D5.0mm | LED1 |  | power |
| 1 | 25.175MHz | Oscillator_DIP-14_DIP-8 | OSC1 |  | 25.175 MHz oscillator, 5 V, in a metal can of either size; its output rated for 50 pF or 10 TTL loads (seven 74F clock inputs and 240 mm of track hang on it, behind R20). The one in stock on 2026-11-19: CTS MXO45HS-3C-25M1750, the half-size can (13.2 mm square, four pins on an 8-pin DIP's corners: 1, 4 ground, 5 the output, 8 VCC), +/-50 ppm, -20 to +70 C; the full-size MXO45-3C-25M1750 was to be had by the thousand only. THE HALF-SIZE CAN at the outline's upper end with the card standing, above the line across it, its pin 1 at the upper 1; it is square and goes in four ways, one of them right. THE FULL-SIZE CAN over the whole outline, its pin 1 at the lower 1. Turned half round either has VCC on its ground pin and on its output. The can's pin 1 is tied to +5 V on the board: on the MXO45 and MXO45HS it is not connected, on the MXO45T and MXO45HST it is an enable, the output on with pin 1 high or open and off with it low, so each of the four runs (CTS's sheet 008-0258-0 rev. M). NOT a can whose output is off with pin 1 high: read pin 1's line in the data sheet of any other make. In a socket: the oscillator socket of the can's size (half-size: Aries 1108800), or four single socket pins in the four holes of the can that is used. NO SOCKET PIN IN THE OTHER TWO HOLES: under a full-size can the two middle holes are +5 V and the can's case is its ground pin, so a socket pin standing there shorts the supply |
| 1 | 330 | R_Axial_DIN0207_L6.3mm_D2.5mm_P10.16mm_Horizontal | R1 |  | PWR LED |
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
